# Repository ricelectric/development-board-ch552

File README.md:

# development-board-ch552

This is an open source repository for a development board based on CH552T. More information is available [here](https://qiita.com/ricelectric/items/80f6da4ddb67f7041b77).

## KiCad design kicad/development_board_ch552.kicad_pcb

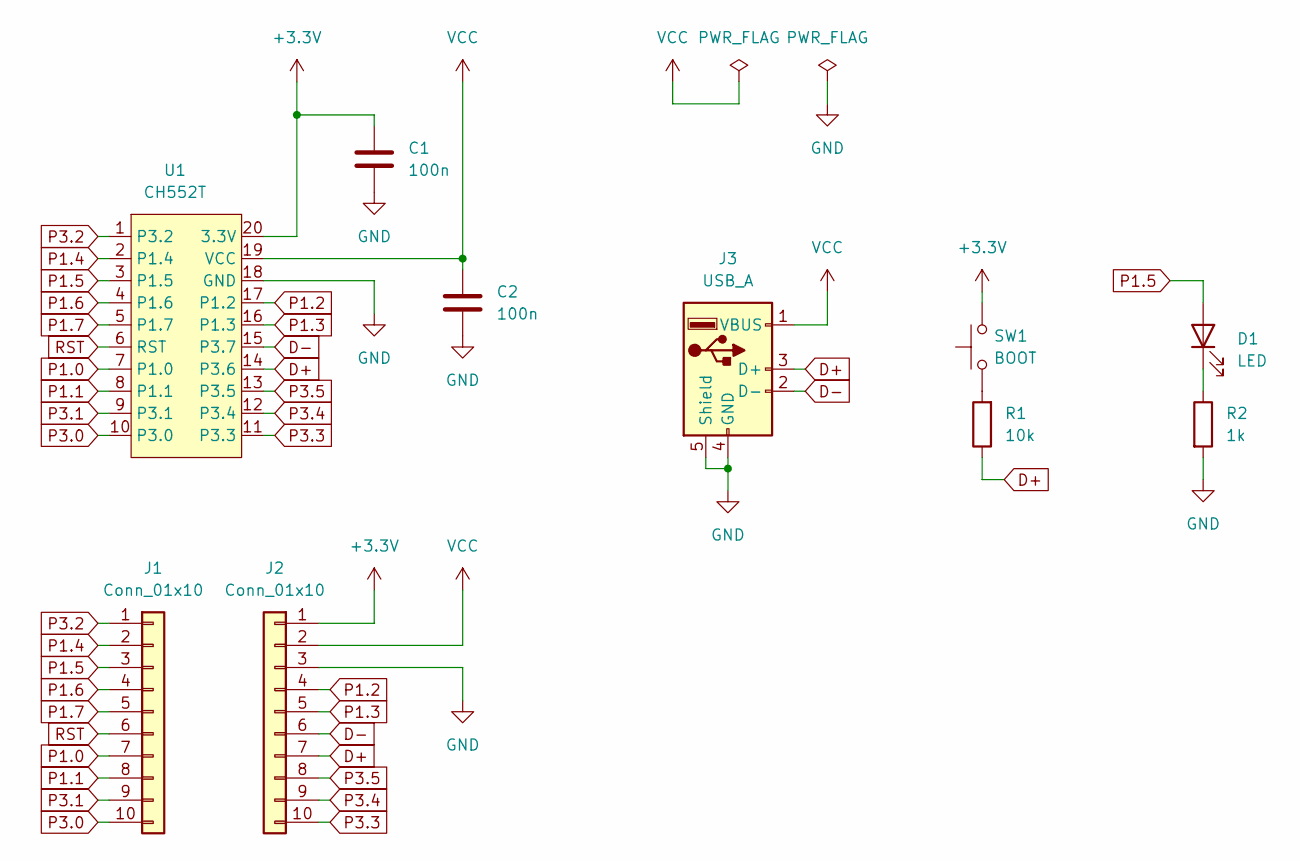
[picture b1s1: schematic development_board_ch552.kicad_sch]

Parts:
C1, C2: 100n; C_0805_2012Metric_Pad1.18x1.45mm_HandSolder
D1: LED; LED_0402_1005Metric_Pad0.77x0.64mm_HandSolder
J1, J2: Conn_01x10; PinHeader_1x10_P2.54mm_Vertical
J3: USB_A; USB_A_UseconnElectronics_USB-4AM103AS_Horizontal
R1: 10k; R_0603_1608Metric_Pad0.98x0.95mm_HandSolder
R2: 1k; R_0603_1608Metric_Pad0.98x0.95mm_HandSolder
SW1: BOOT; SW_Push_SPST_NO_TVAF06-A020B-R
U1: CH552T; TSSOP-20_4.4x6.5mm_P0.65mm

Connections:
+3.3V: C1.1, J2.1, SW1.2, U1.20 (3.3V)
D+: J2.7, J3.3 (D+), R1.1, U1.14 (P3.6)
D-: J2.6, J3.2 (D-), U1.15 (P3.7)
GND: C1.2, C2.2, J2.3, J3.4 (GND), J3.5 (Shield), R2.2, U1.18 (GND)
unnamed: D1.1 (K), R2.1
unnamed: R1.2, SW1.1
P1.0: J1.7, U1.7 (P1.0)
P1.1: J1.8, U1.8 (P1.1)
P1.2: J2.4, U1.17 (P1.2)
P1.3: J2.5, U1.16 (P1.3)
P1.4: J1.2, U1.2 (P1.4)
P1.5: D1.2 (A), J1.3, U1.3 (P1.5)
P1.6: J1.4, U1.4 (P1.6)
P1.7: J1.5, U1.5 (P1.7)
P3.0: J1.10, U1.10 (P3.0)
P3.1: J1.9, U1.9 (P3.1)
P3.2: J1.1, U1.1 (P3.2)
P3.3: J2.10, U1.11 (P3.3)
P3.4: J2.9, U1.12 (P3.4)
P3.5: J2.8, U1.13 (P3.5)
RST: J1.6, U1.6 (RST)
VCC: C2.1, J2.2, J3.1 (VBUS), U1.19 (VCC)

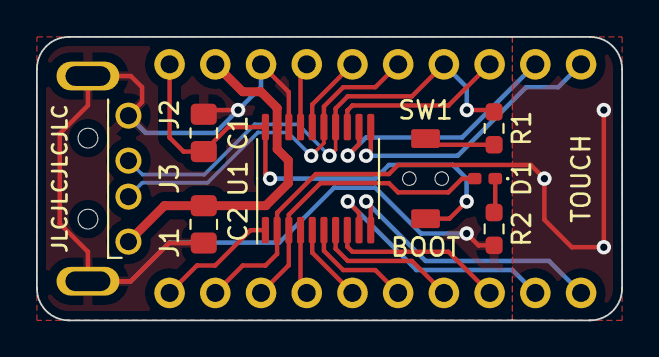
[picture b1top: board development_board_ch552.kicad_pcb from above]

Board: 2 copper layers, 32.5 x 15.7 mm, 10 parts (0 on the bottom side), 22 nets.

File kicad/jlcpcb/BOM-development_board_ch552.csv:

Comment,Designator,Footprint,LCSC
100n,C2,C_0805_2012Metric_Pad1.18x1.45mm_HandSolder,
100n,C1,C_0805_2012Metric_Pad1.18x1.45mm_HandSolder,
Conn_01x10,J1,PinHeader_1x10_P2.54mm_Vertical,
1k,R2,R_0603_1608Metric_Pad0.98x0.95mm_HandSolder,
USB_A,J3,USB_A_UseconnElectronics_USB-4AM103AS_Horizontal,
CH552T,U1,TSSOP-20_4.4x6.5mm_P0.65mm,
LED,D1,LED_0402_1005Metric_Pad0.77x0.64mm_HandSolder,
BOOT,SW1,SW_Push_SPST_NO_TVAF06-A020B-R,
Conn_01x10,J2,PinHeader_1x10_P2.54mm_Vertical,
10k,R1,R_0603_1608Metric_Pad0.98x0.95mm_HandSolder,
